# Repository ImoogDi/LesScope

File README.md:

# LesScope
Arduino based Dual Channel Scope for eurorack-modular synths.

**Table of Contents**

- [Introduction](#intro)
- [Construction Guide](./doc/constructionguide.md)
- [LesScope-Menu](#menu)
- [Technical data](#technical-data)
- [References](#references)
- [License](#license)

## Introduction

This eurorack-modul is designed for modular-synthesizers as dual channel scope modul.  
Only two active parts are required to sample the signal at the jack-inputs.  
 1. Arduino Nano V3.x.  
 2. Quad Op Amp MCP6004 rail-to-rail input/output.  

The Arduino Nano samples the amplified signal on two 10-Bit A/D multiplexed inputs.  
Sampled-data are then traced on the 1.3'' OLED display.  
Dataentry and menu-selections are possible with that encoder <u>Select</u>.  
AC/DC coupling is selectable for both channels on two switches.  
Every channel has two jacks linked together for signal-input and routing to other inputs.  
That signal on <u>Channel1</u> is normalized to the <u>Trigger</u> input-jack.  
With an additonal cable plugged into the <u>Trigger</u> jack a different trigger-signal can be used.  

All parts are common available and DIY-friendly designed.   
(Details see attached pictures)  

- Modul Frontpanel  

- Modul Backside  

- Modul Right side  

- Modul Left side  

- Dual Trace example  

## LesScope-Menu
- Menu example  

## Technical data

- size:  
  height: 3VP (133,35mm)  
  width : 8HP ( 40,3mm)  
  depth : 35mm

- power:  
   +5Volt, 0 mA  
  +12Volt, 45mA  
  -12Volt, 0 mA  

- display:  
    128x64 pixel 1.3inch OLED with SPI interface  

- MCU:  
    Arduino Nano V3.x ATmega 328P  

- Electrical features:  
    Rotary encoder with push-button.  
    Two separate channels with AC/DC-coupling.  
    Input Voltage 10Vp-p for both channels.  
    Menu selectable signal-amplification (1...4:Channel1; 1...2:Channel2).  
    Sampling-rate range: 50us...100msec on both channels.  
    Separate trigger-input (default linked to <u>Channel1</u>).  

- Measurement-capabilities (only on <u>Channel1</u>):  
    Frequency-measurement range: ~10Hz...~6000Hz.  
    Tuning-check range: C0(16.35Hz)...C8(4186.01Hz).  

There are fife 3.5mm jacks available with following functions.  
<table>
<tr>
    <th>Jack-Name</th>
    <th>Function</th>
    <th>Comment</th>
</tr>
<tr>
    <td>Channel1 (two jacks)</td>
    <td>Signal input for <u>Channel1</u></td>
    <td>the two jacks are linked together and <br>this signal is normalized to <u>Trigger</u> input.</td>
</tr>
<tr>
    <td>Channel2 (two jacks)</td>
    <td>Signal input for <u>Channel2</u></td>
    <td>the two jacks are linked together.</td>
</tr>
<tr>
    <td>Trigger</td>
    <td>Signal input for <u>Trigger</u></td>
    <td>this signal is normalized to <u>Channel1</u>.</td>
</tr>
</table>

## References

* [mzuelch Display](https://github.com/mzuelch/CATs-Eurosynth/tree/main/Modules/HAGIWO/Display)
* [frequency measure](http://www.pjrc.com/teensy/td_libs_FreqMeasure.html)
* [encoder](http://www.pjrc.com/teensy/td_libs_Encoder.html)
* [Adafruit SH110X display-driver](https://github.com/adafruit/Adafruit_SH110X/actions)
* [midi conversion table](https://musicinformationretrieval.com/midi_conversion_table.html)

## License
> Hardware:cc by-nc-sa 4.0  ([details](https://creativecommons.org/licenses/by-nc-sa/4.0/))  
> Software:licensed under GPL-3.0 ([details](https://www.gnu.org/licenses/gpl-3.0.html.en))

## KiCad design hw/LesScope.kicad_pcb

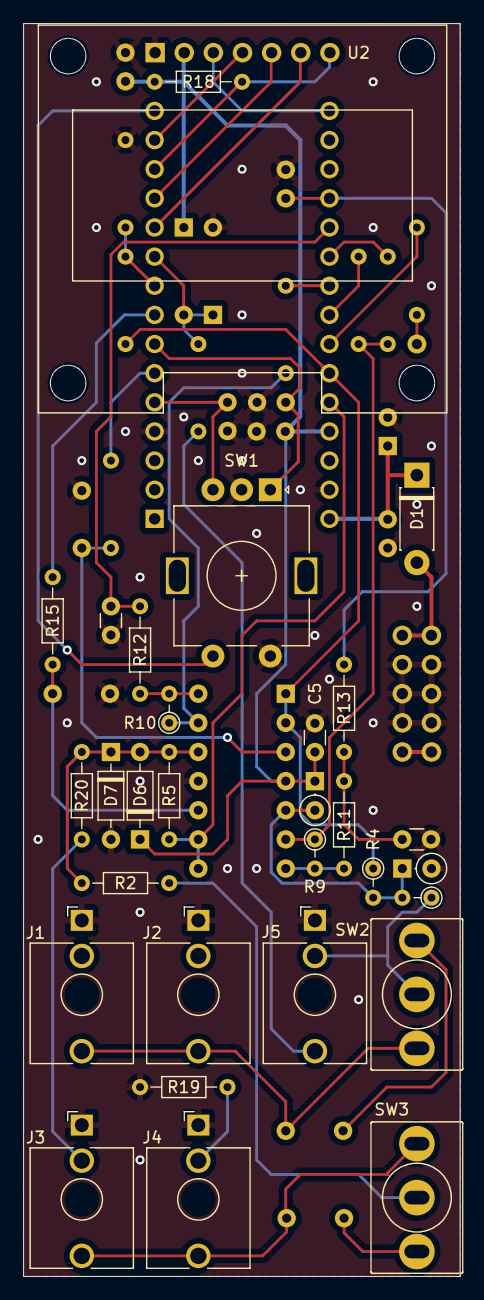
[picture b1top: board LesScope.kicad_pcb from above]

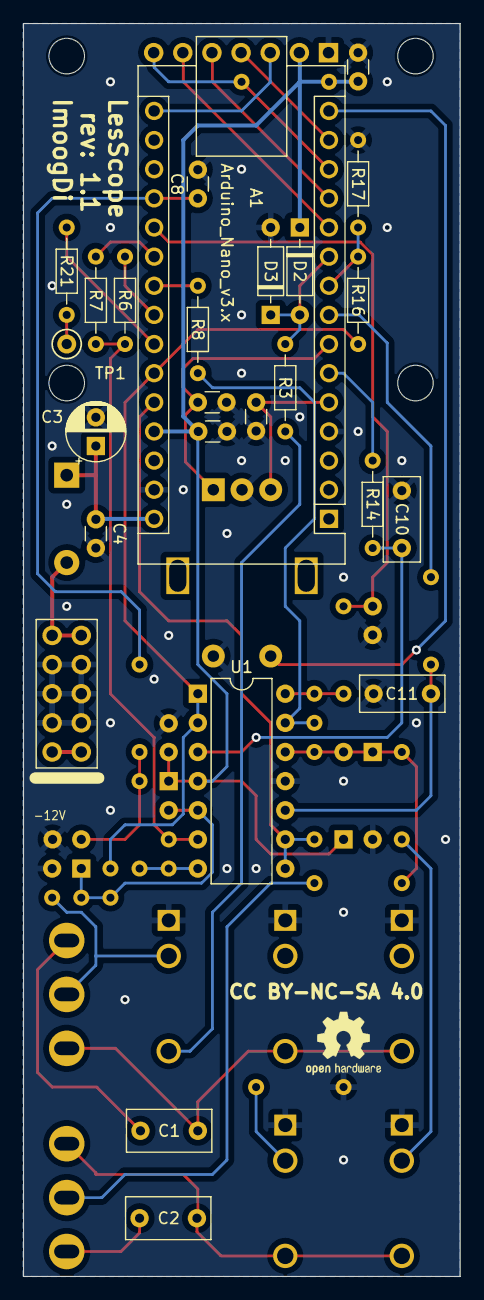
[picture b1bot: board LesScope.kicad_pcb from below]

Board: 2 copper layers, 38.1 x 109.2 mm, 56 parts (26 on the bottom side), 44 nets.

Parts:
A1: Arduino_Nano_v3.x; Arduino_Nano
C1, C2: 2,2uF; C_Rect_L7.2mm_W3.5mm_P5.00mm_FKS2_FKP2_MKS2_MKP2
C3: 22u; CP_Radial_D5.0mm_P2.50mm
C4, C5, C6, C14: 100nF; C_Disc_D3.0mm_W1.6mm_P2.50mm
C7, C8: 27nF; C_Disc_D3.0mm_W1.6mm_P2.50mm
C9, C12, C13: 10nF; C_Disc_D3.0mm_W1.6mm_P2.50mm
C10, C11: 1uF; C_Rect_L7.2mm_W3.0mm_P5.00mm_FKS2_FKP2_MKS2_MKP2
D1: 1N5817; D_DO-41_SOD81_P7.62mm_Horizontal
D2, D3, D6, D7: BAT46; D_DO-35_SOD27_P7.62mm_Horizontal
D4, D5: BAT46; D_DO-35_SOD27_P2.54mm_Vertical_KathodeUp
J1, J2, J3, J4, J5: AudioJack2_SwitchT; Jack_3.5mm_QingPu_WQP-PJ398SM_Vertical_CircularHoles
J6: Conn_02x05_Odd_Even; Pins_2x05_2.54mm_TH_Europower
R1: 100K; R_Axial_DIN0204_L3.6mm_D1.6mm_P2.54mm_Vertical
R2: 100K; R_Axial_DIN0204_L3.6mm_D1.6mm_P7.62mm_Horizontal
R3, R16, R20: 4,7K; R_Axial_DIN0204_L3.6mm_D1.6mm_P7.62mm_Horizontal
R4: 47K; R_Axial_DIN0204_L3.6mm_D1.6mm_P2.54mm_Vertical
R5, R14, R15: 47K; R_Axial_DIN0204_L3.6mm_D1.6mm_P7.62mm_Horizontal
R6: 4,99K; R_Axial_DIN0204_L3.6mm_D1.6mm_P7.62mm_Horizontal
R7, R8, R17, R18: 10K; R_Axial_DIN0204_L3.6mm_D1.6mm_P7.62mm_Horizontal
R9, R10: 10K; R_Axial_DIN0204_L3.6mm_D1.6mm_P2.54mm_Vertical
R11, R13, R21: 1K; R_Axial_DIN0204_L3.6mm_D1.6mm_P7.62mm_Horizontal
R12: 2.7K; R_Axial_DIN0204_L3.6mm_D1.6mm_P7.62mm_Horizontal
R19: 27K; R_Axial_DIN0204_L3.6mm_D1.6mm_P7.62mm_Horizontal
REF_A: OSHW-Logo2_7.3x6mm_SilkScreen
SW1: RotaryEncoder_Switch; RotaryEncoder_Alps_EC11E-Switch_Vertical_H20mm
SW2, SW3: SW_SPDT; Switch_Toggle_SPDT_Mini_SolderLug
TP1: TestPoint; TestPoint_WireHole
U1: MCP6004; DIP-14_W7.62mm
U2: OLED 1.3 128X64 SPI; DisplayModule_DM_OLED13

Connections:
+5V: A1.27 (+5V), C5.1, C6.1, C14.2, D2.1 (K), D4.1 (K), D6.1 (K), R18.1, U1.4 (V+), U2.2 (VDD)
+12V: A1.30 (VIN), C3.1, C4.1, D1.1 (K)
+12VA: D1.2 (A), J6.1, J6.2
-12VA: J6.9, J6.10
/Backplane/In1: D4.2 (A), D5.1 (K), R1.2, R4.2, U1.5 (+)
/Backplane/In2: D6.2 (A), D7.1 (K), R2.2, R5.2, R20.2, U1.12 (+)
/Backplane/Trigger: J5.T, R3.1
/Display/CS: A1.13 (D10), R18.2, U2.7 (CS:chip-select)
/Display/DC_data_cmd: A1.11 (D8), U2.6 (DC:data/command)
/Display/DI_SDA: A1.14 (D11), U2.4 (SDA:Mosi_data)
/Display/DO_SCK: A1.16 (D13), U2.3 (SCK:CLK_clock)
/Display/RST: A1.12 (D9), U2.5 (RES:Reset)
/Encoder.ENC_A: A1.7 (D4), C12.1, SW1.A
/Encoder.ENC_B: A1.5 (D2), C13.1, SW1.B
/Encoder.ENC_SW: A1.15 (D12), SW1.S1
/Input_Conditioner/AD_In1: A1.19 (A0), C8.1, R13.2
/Input_Conditioner/AD_In2: A1.20 (A1), C9.1, R12.2
/Input_Conditioner/AMP1_x2: A1.21 (A2), R7.2
/Input_Conditioner/AMP1_x3: A1.23 (A4), R6.2
/Input_Conditioner/AMP2_x2: A1.22 (A3), R8.2
/Input_Conditioner/Chan1_Offset: A1.25 (A6), R4.1, R16.1, U1.1, U1.2 (-)
/Input_Conditioner/Chan2_Offset: A1.26 (A7), R5.1, U1.8, U1.9 (-)
/Input_Conditioner/Fast_PWM1: A1.6 (D3), R14.1
/Input_Conditioner/Fast_PWM2: A1.8 (D5), R15.1
/Input_Conditioner/Trigger_MCU: A1.10 (D7), D2.2 (A), D3.1 (K), R3.2
GND: A1.4 (GND), A1.29 (GND), C3.2, C4.2, C5.2, C6.2, C7.2, C8.2, C9.2, C10.2, C11.2, C12.2, C13.2, C14.1, D3.2 (A), D5.2 (A), D7.2 (A), J1.S, J2.S, J3.S, J4.S, J5.S, J6.3, J6.4, J6.5, J6.6, J6.7, J6.8, R17.1, R19.2, SW1.C, SW1.S2, U1.11 (V-), U2.1 (GND)
In1_SW: J5.TN, R1.1, SW2.2 (B)
unnamed: A1.24 (A5), R21.1
unnamed: A1.9 (D6), R16.2, R17.2
unnamed: C7.1, R11.2, R13.1
unnamed: J3.TN, R20.1
unnamed: J4.TN, R19.1
unnamed: R10.2, R12.1, U1.14
unnamed: R9.2, R11.1, U1.7
unnamed: R21.2, TP1.1
unnamed: C1.1, SW2.1 (A)
unnamed: C1.2, J1.T, J2.T, SW2.3 (C)
unnamed: C2.1, SW3.1 (A)
unnamed: R2.1, SW3.2 (B)
unnamed: C2.2, J3.T, J4.T, SW3.3 (C)
unnamed: C10.1, R14.2, U1.3 (+)
unnamed: R6.1, R7.1, R9.1, U1.6 (-)
unnamed: C11.1, R15.2, U1.10 (+)
unnamed: R8.1, R10.1, U1.13 (-)

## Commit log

2025-03-19 LesScope first release.
2025-03-19 readme update
2025-03-20 hw and sw added
2025-03-20 Update issue templates
2025-03-21 frontpanel added
2025-07-17 update for issues:#2 & #3
2025-07-18 comment update
2025-07-18 doc update
